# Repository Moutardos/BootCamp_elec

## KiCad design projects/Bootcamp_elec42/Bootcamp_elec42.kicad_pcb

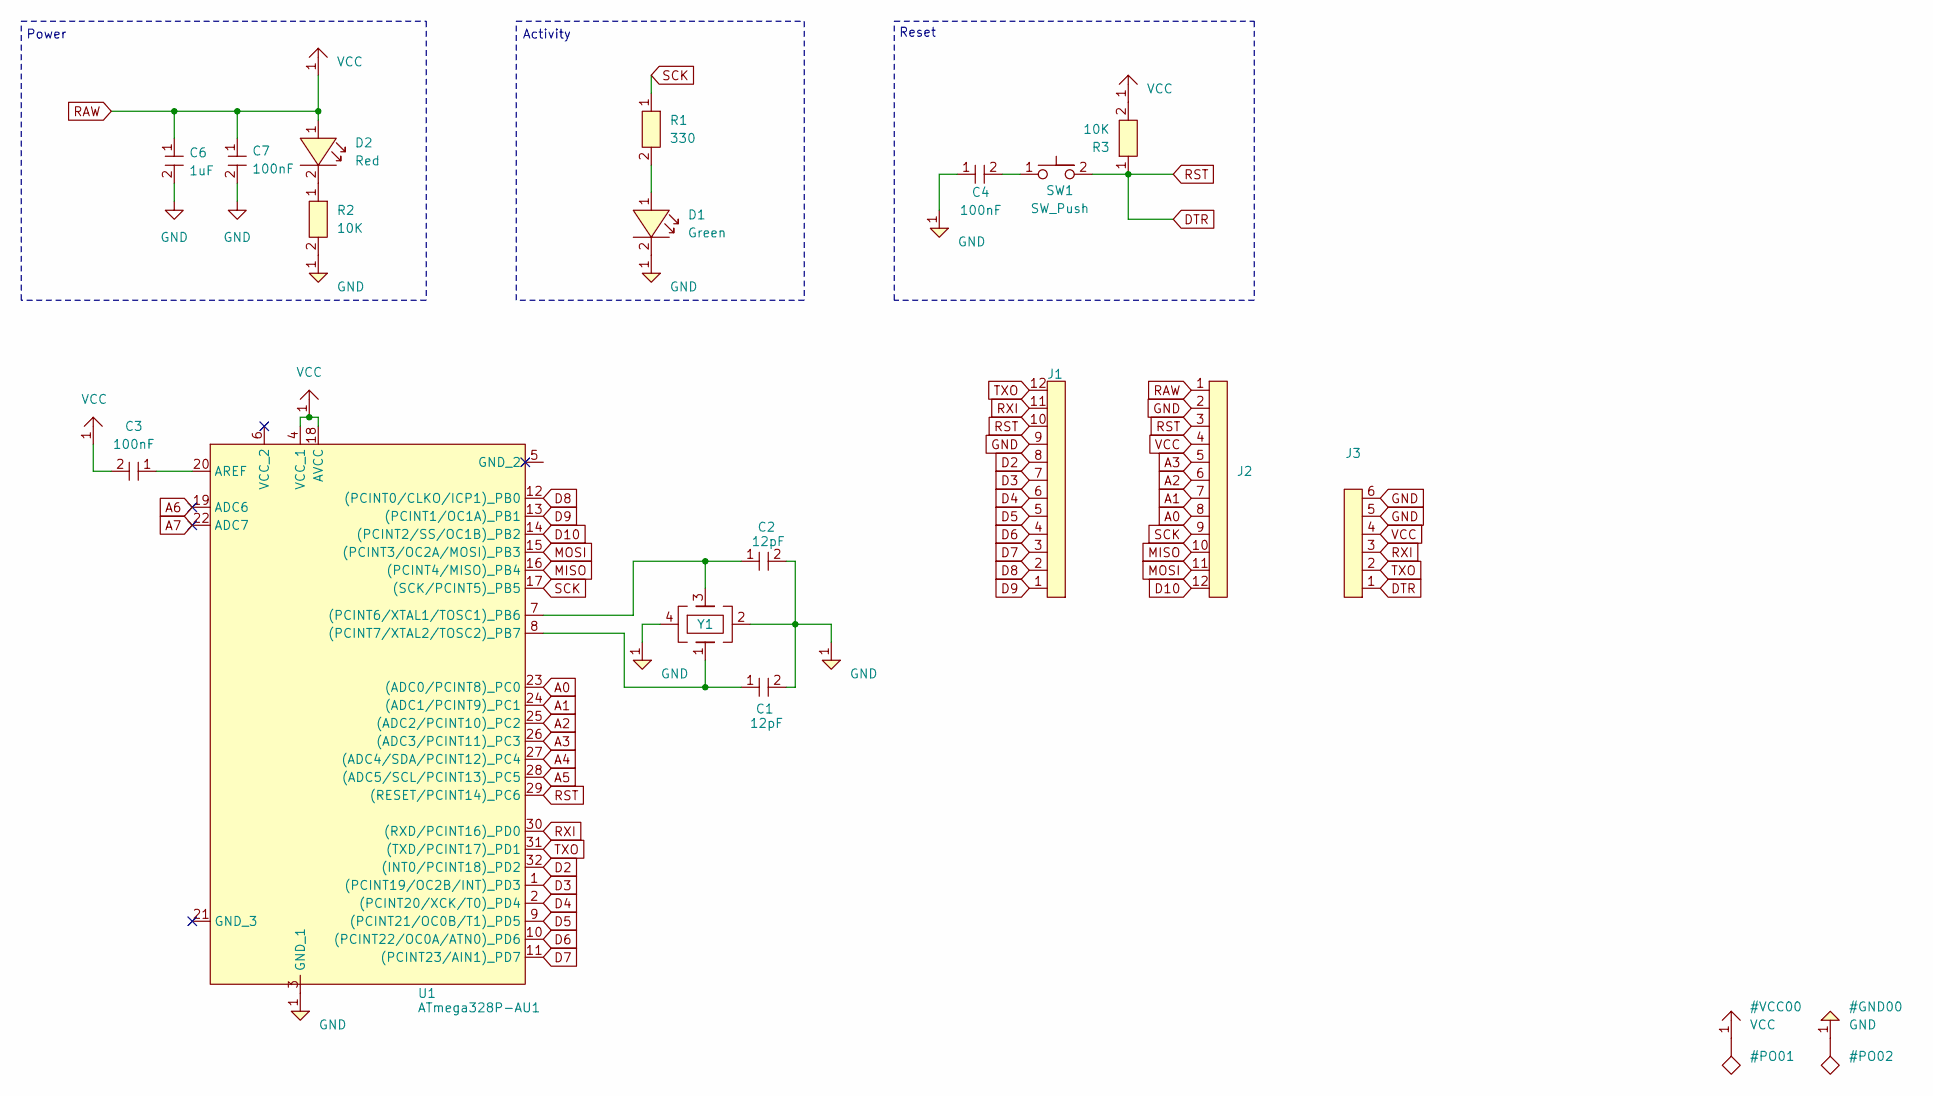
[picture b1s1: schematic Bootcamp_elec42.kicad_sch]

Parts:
ATmega328P-AU1: U1; ATMEGA328P; LCSC Part Number C14877
C1, C2: 12pF; CR_Generic; LCSC Part Number C38523
C3, C4, C7: 100nF; CR_Generic; LCSC Part Number C14663
C6: 1uF; CR_Generic; LCSC Part Number C15849
D1: Green; LED_generic; LCSC Part Number C916074
D2: Red; LED_generic; LCSC Part Number C965799
J1, J2: PinHeader_12
J3: PinHeader_6
R1: 330; CR_Generic; LCSC Part Number C23138
R2, R3: 10K; CR_Generic; LCSC Part Number C98220
SW1: SW_Push; SW_B3U1000P; LCSC Part Number C231329
Y1: Crystal_YSX321SL; LCSC Part Number C13738

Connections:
A0: ATmega328P-AU1.23 ((ADC0/PCINT8)_PC0), J2.8
A1: ATmega328P-AU1.24 ((ADC1/PCINT9)_PC1), J2.7
A2: ATmega328P-AU1.25 ((ADC2/PCINT10)_PC2), J2.6
A3: ATmega328P-AU1.26 ((ADC3/PCINT11)_PC3), J2.5
A4: ATmega328P-AU1.27 ((ADC4/SDA/PCINT12)_PC4)
A5: ATmega328P-AU1.28 ((ADC5/SCL/PCINT13)_PC5)
A6: ATmega328P-AU1.19 (ADC6)
A7: ATmega328P-AU1.22 (ADC7)
D2: ATmega328P-AU1.32 ((INT0/PCINT18)_PD2), J1.8
D3: ATmega328P-AU1.1 ((PCINT19/OC2B/INT)_PD3), J1.7
D4: ATmega328P-AU1.2 ((PCINT20/XCK/T0)_PD4), J1.6
D5: ATmega328P-AU1.9 ((PCINT21/OC0B/T1)_PD5), J1.5
D6: ATmega328P-AU1.10 ((PCINT22/OC0A/ATN0)_PD6), J1.4
D7: ATmega328P-AU1.11 ((PCINT23/AIN1)_PD7), J1.3
D8: ATmega328P-AU1.12 ((PCINT0/CLKO/ICP1)_PB0), J1.2
D9: ATmega328P-AU1.13 ((PCINT1/OC1A)_PB1), J1.1
D10: ATmega328P-AU1.14 ((PCINT2/SS/OC1B)_PB2), J2.12
DTR: ATmega328P-AU1.29 ((RESET/PCINT14)_PC6), J1.10, J2.3, J3.1, R3.1, SW1.2
MISO: ATmega328P-AU1.16 ((PCINT4/MISO)_PB4), J2.10
MOSI: ATmega328P-AU1.15 ((PCINT3/OC2A/MOSI)_PB3), J2.11
unnamed: ATmega328P-AU1.7 ((PCINT6/XTAL1/TOSC1)_PB6), C2.1, Y1.3
unnamed: ATmega328P-AU1.8 ((PCINT7/XTAL2/TOSC2)_PB7), C1.1, Y1.1
unnamed: ATmega328P-AU1.20 (AREF), C3.1
unnamed: C4.2, SW1.1
unnamed: D1.1, R1.2
unnamed: D2.2, R2.1
RXI: ATmega328P-AU1.30 ((RXD/PCINT16)_PD0), J1.11, J3.3
SCK: ATmega328P-AU1.17 ((SCK/PCINT5)_PB5), J2.9, R1.1
TXO: ATmega328P-AU1.31 ((TXD/PCINT17)_PD1), J1.12, J3.2

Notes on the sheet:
Activity
Reset
Power

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
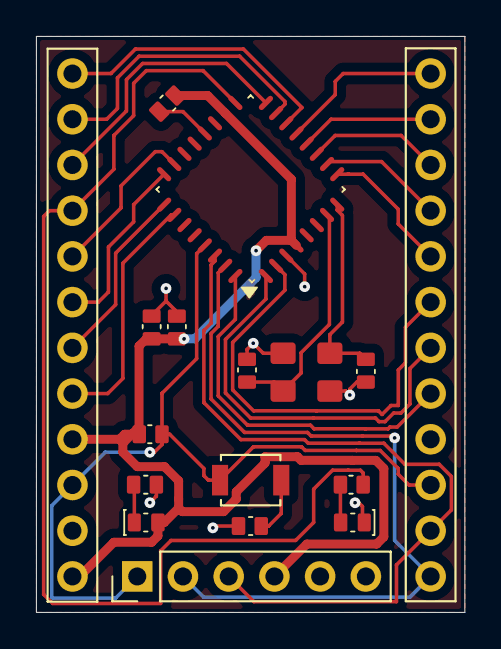
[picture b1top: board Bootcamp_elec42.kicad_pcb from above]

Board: 2 copper layers, 23.8 x 32.0 mm, 17 parts (0 on the bottom side), 27 nets.

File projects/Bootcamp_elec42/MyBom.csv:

"LCSC Part Number","Value","Reference","Footprint","Description","Qty"
"C14877","U1","ATmega328P-AU1","Footprint:ATMEGA328P","AVR 20MHz 23 TQFP-32(7x7) Microcontrollers RoHS","1"
"C38523","12pF","C1,C2","Footprint:CR_Generic","50V 12pF C0G ±5% 0603 Ceramic Capacitors RoHS","2"
"C14663","100nF","C3,C4,C7","Footprint:CR_Generic","50V 100nF X7R ±10% 0603 Ceramic Capacitors RoHS","3"
"C15849","1uF","C6","Footprint:CR_Generic","50V 1uF X5R ±10% 0603 Ceramic Capacitors RoHS","1"
"C916074","Green","D1","Footprint:LED_generic","20mA 50mcd 570nm~575nm Yellow Green 1.9V~2.4V 60mW 0603 LED Indication - Discrete RoHS","1"
"C965799","Red","D2","Footprint:LED_generic","20mA 225mcd op View Mount 620nm~630nm Red 2.3V 50mW 0603 LED Indication - Discrete RoHS","1"
"","~","J1,J2","Footprint:PinHeader_12","Pin header size 12","2"
"","~","J3","Footprint:PinHeader_6","Pin header size 6","1"
"C23138","330","R1","Footprint:CR_Generic","100mW 330Ω 75V ±100ppm/℃ Thick Film Resistor ±1% 0603 Chip Resistor - Surface Mount RoHS","1"
"C98220","10K","R2,R3","Footprint:CR_Generic","100mW 10kΩ 75V ±100ppm/℃ Thick Film Resistor ±1% 0603 Chip Resistor - Surface Mount RoHS","2"
"C231329","SW_Push","SW1","Footprint:SW_B3U1000P","12V 2.5mm Round Button 3mm SPST 50mA SMD,3x2.5mm Tactile Switches RoHS","1"
"C13738","~","Y1","Footprint:Crystal_YSX321SL","Crystal Oscillator 9pF SMD3225-4P Crystals RoHS","1"

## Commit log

2025-11-18 [ADD] .gitignore ReadMe
2025-11-18 [ADD] Bills of material & schema
2025-11-19 Docker compose for kicad + Symbols done for: C, Y, R and MCU
2025-11-19 [ADD] Symbols for diodes, switches and for the 42board
2025-11-21 [ADD] Symbols finished, schematic done
2025-11-22 [ADD] Started footprint: C-R
2025-11-22 [ADD] Footprint
2025-11-27 SMD Done~
2025-11-27 Files needed
